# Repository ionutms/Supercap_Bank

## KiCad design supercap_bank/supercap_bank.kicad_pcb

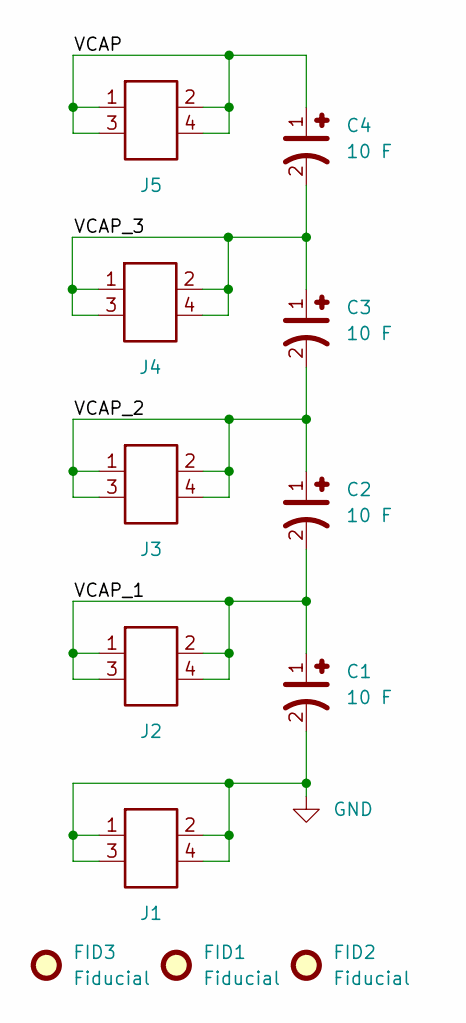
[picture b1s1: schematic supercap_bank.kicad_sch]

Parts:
C1, C2, C3, C4: 10 F; C_197x394_H31_5_5_0x10Metric; Tolerance 10%; Voltage Rating 2.7V; MPN HV1030-2R7106-R
FID1, FID2, FID3: Fiducial; Fiducial_0.5mm_Mask1mm
J1, J2, J3, J4, J5: FTSH-102-04-L-DH; Current Rating (A) 5.2; Voltage Rating (V) 300; MPN FTSH-102-04-L-DH

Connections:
/VCAP: C4.1, J5.1, J5.2, J5.3, J5.4
/VCAP_1: C1.1, C2.2, J2.1, J2.2, J2.3, J2.4
/VCAP_2: C2.1, C3.2, J3.1, J3.2, J3.3, J3.4
/VCAP_3: C3.1, C4.2, J4.1, J4.2, J4.3, J4.4
GND: C1.2, J1.1, J1.2, J1.3, J1.4

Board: 4 copper layers, 12 parts (5 on the bottom side), 5 nets, no tracks yet.

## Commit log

2026-01-01 Add KiCad project files for supercapacitor bank
2026-01-01 Add KiCAD_Symbols_Generator as a submodule
2026-01-01 Add KiCad library table files
2026-01-01 Update KiCad project files
2026-01-01 chore: update workflows and kicad config from central repository
2026-01-01 Update KiCad documentation for supercap_bank (schematics and PCB renders)
2026-01-01 Update KiCad config and submodule
2026-01-01 Update KiCad configuration
2026-01-01 Update KiCAD configuration file
2026-01-01 Update KiCAD configuration and project files
2026-01-03 Update KiCAD project files and submodule
